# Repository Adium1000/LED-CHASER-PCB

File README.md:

# LED CHASER 
### Samples
### PCB Done

### PCB

### PCB DESIGN

### Schematics

A small 10x LED chaser that is using the a
- a timer ic
- a 4017 ic

# BOM
| Quantity | Component           |
|:--------:|:-------------------:|
| 10        | LEDs 3mm  | 
| 1        | 50k Potentiometer|
| 1        | 470 Ohm Rezistor | 
| 1       | 1k Rezistor       |
| 1        | 0.01 uF Capacitator|
| 1        |1 uF Capacitator  | 
| 1        |4017 IC  | 
| 1        |NE555P IC  |

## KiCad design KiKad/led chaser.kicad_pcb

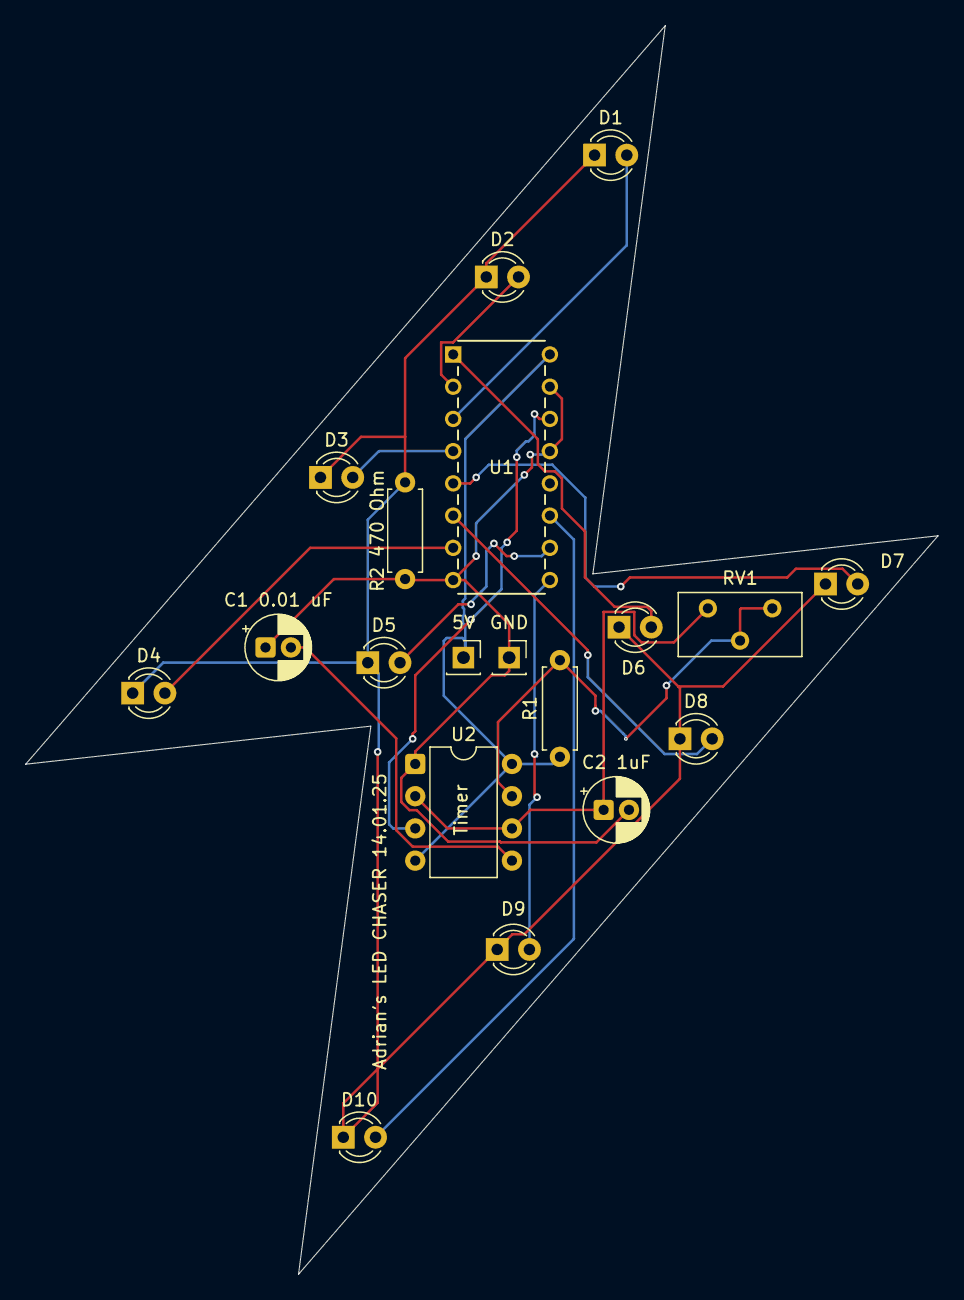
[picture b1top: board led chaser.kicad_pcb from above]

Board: 2 copper layers, 71.9 x 98.4 mm, 19 parts (0 on the bottom side), 17 nets.

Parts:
5V: MountingHole_Pad; PinSocket_1x01_P2.54mm_Vertical
C1 0.01 uF: 0.01 uF; CP_Radial_D5.0mm_P2.00mm
C2 1uF: 1 uF; CP_Radial_D5.0mm_P2.00mm
D1, D2, D3, D4, D5, D6, D7, D8, D9, D10: LED; LED_D3.0mm
GND: MountingHole_Pad; PinSocket_1x01_P2.54mm_Vertical
R1: 1k; R_Axial_DIN0207_L6.3mm_D2.5mm_P7.62mm_Horizontal
R2 470 Ohm: 470; R_Axial_DIN0207_L6.3mm_D2.5mm_P7.62mm_Horizontal
RV1: 50K; Potentiometer_Bourns_3296Y_Vertical
U1: 4017; N16
U2: NE555P; DIP-8_W7.62mm

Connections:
+5v: 5V.1, R1.1, U1.16 (VDD), U2.4 (R), U2.8 (VCC)
GND: C1 0.01 uF.1, C2 1uF.2, GND.1, R2 470 Ohm.2, U1.8 (VSS), U1.13 (CKEN), U1.15 (Reset), U2.1 (GND)
unnamed: D1.2 (A), U1.3 (Q0)
unnamed: D1.1 (K), D2.1 (K), D3.1 (K), D4.1 (K), D5.1 (K), D6.1 (K), D7.1 (K), D8.1 (K), D9.1 (K), D10.1 (K), R2 470 Ohm.1
unnamed: D2.2 (A), U1.2 (Q1)
unnamed: D3.2 (A), U1.4 (Q2)
unnamed: D4.2 (A), U1.7 (Q3)
unnamed: D5.2 (A), U1.10 (Q4)
unnamed: D6.2 (A), U1.1 (Q5)
unnamed: D7.2 (A), U1.5 (Q6)
unnamed: D8.2 (A), U1.6 (Q7)
unnamed: D9.2 (A), U1.9 (Q8)
unnamed: D10.2 (A), U1.11 (Q9)
unnamed: C1 0.01 uF.2, U2.5 (CV)
unnamed: R1.2, RV1.1, RV1.2, U2.7 (DIS)
OUT: U1.14 (CLK), U2.3 (Q)
TR: C2 1uF.1, RV1.3, U2.2 (TR), U2.6 (THR)

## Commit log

2026-01-14 Uploaded Assets
2026-01-14 Added the README description + BOM.CSV
2026-01-15 small changes
2026-01-15 error fixed
2026-01-15 another fix
2026-01-15 What?
2026-01-15 done
